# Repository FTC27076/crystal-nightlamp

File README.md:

Hi! 
this is my week 2 project in half-life and this week I'm designing a night light in the shape of a crystal!
Here's how it works:
a 4XAA battery holder with a switch carries the power to a 220 ohm resistor, which then goes to a 5V green LED strip
## Onshape Link:
https://cad.onshape.com/documents/a97c7134ccd0741b3f998674/w/13b3333805ea5d17c64ad727/e/1efaff581b8b39a1d64b4fe4

## BOM:

| Item | Qty | Supplier | Cost/item | Total Cost | link |
| :--- | :--- | :--- | :--- | :--- | :--- |
| resistor pack | 1 | E projects, LLC | $6.42 | $6.42 | https://www.amazon.ca/Projects-10EP514220R-220-Resistors-Pack/dp/B00CVZ3YOQ?source=ps-sl-shoppingads-lpcontext&ref_=fplfs&psc=1&smid=AODFMOUHD0RRM |
| LED strip lights | 1 | clearhill | $10.53 | $10.53 | https://www.amazon.ca/Clearhill-Dimmable-320LEDs-Waterproof-Decoration/dp/B0CZ6RRBV5?source=ps-sl-shoppingads-lpcontext&ref_=fplfs&th=1 |
| DAIERTEK 4 AA Battery Holder with Switch 6V Battery Case Holder with Cover 4 Slots 1.5V AA Battery Storage Box with Wire | 1 | DAIERTEK | $7.00 | $7.00 | https://www.amazon.ca/DaierTek-Battery-Holder-Storage-Connector/dp/B09N1GDWQ9?source=ps-sl-shoppingads-lpcontext&ref_=fplfs&smid=AVZNWT0O79W01&th=1 |
| 3d print/model | 1 | Snapmaker | $0.01 | $0.01 | https://cad.onshape.com/documents/a97c7134ccd0741b3f998674/w/13b3333805ea5d17c64ad727/e/1efaff581b8b39a1d64b4fe4 |
| PCB | 1 | JLC | $13.89 | $13.89 | https://trade.jlcpcb.com/checkout/payMethod?systemType=order_pcb&calType=PAY&batchNum=W2026112710500528&preOfferRate=0&spm=Jlcpcb.Confirmorder.1001 |
| Estimated total shipping | 1 | | | $7.03 | |

Images of the design ig:

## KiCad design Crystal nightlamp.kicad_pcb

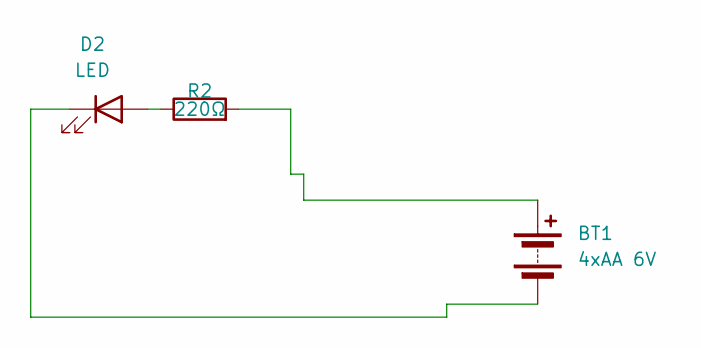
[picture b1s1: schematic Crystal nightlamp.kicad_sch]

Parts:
BT1: 4xAA 6V; SolderWire-0.5sqmm_1x02_P4.8mm_D0.9mm_OD2.3mm
D2: LED; LED_D3.0mm
R2: 220Ω; R_Axial_DIN0204_L3.6mm_D1.6mm_P5.08mm_Horizontal

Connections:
unnamed: BT1.1 (+), R2.2
unnamed: BT1.2 (-), D2.1 (K)
unnamed: D2.2 (A), R2.1

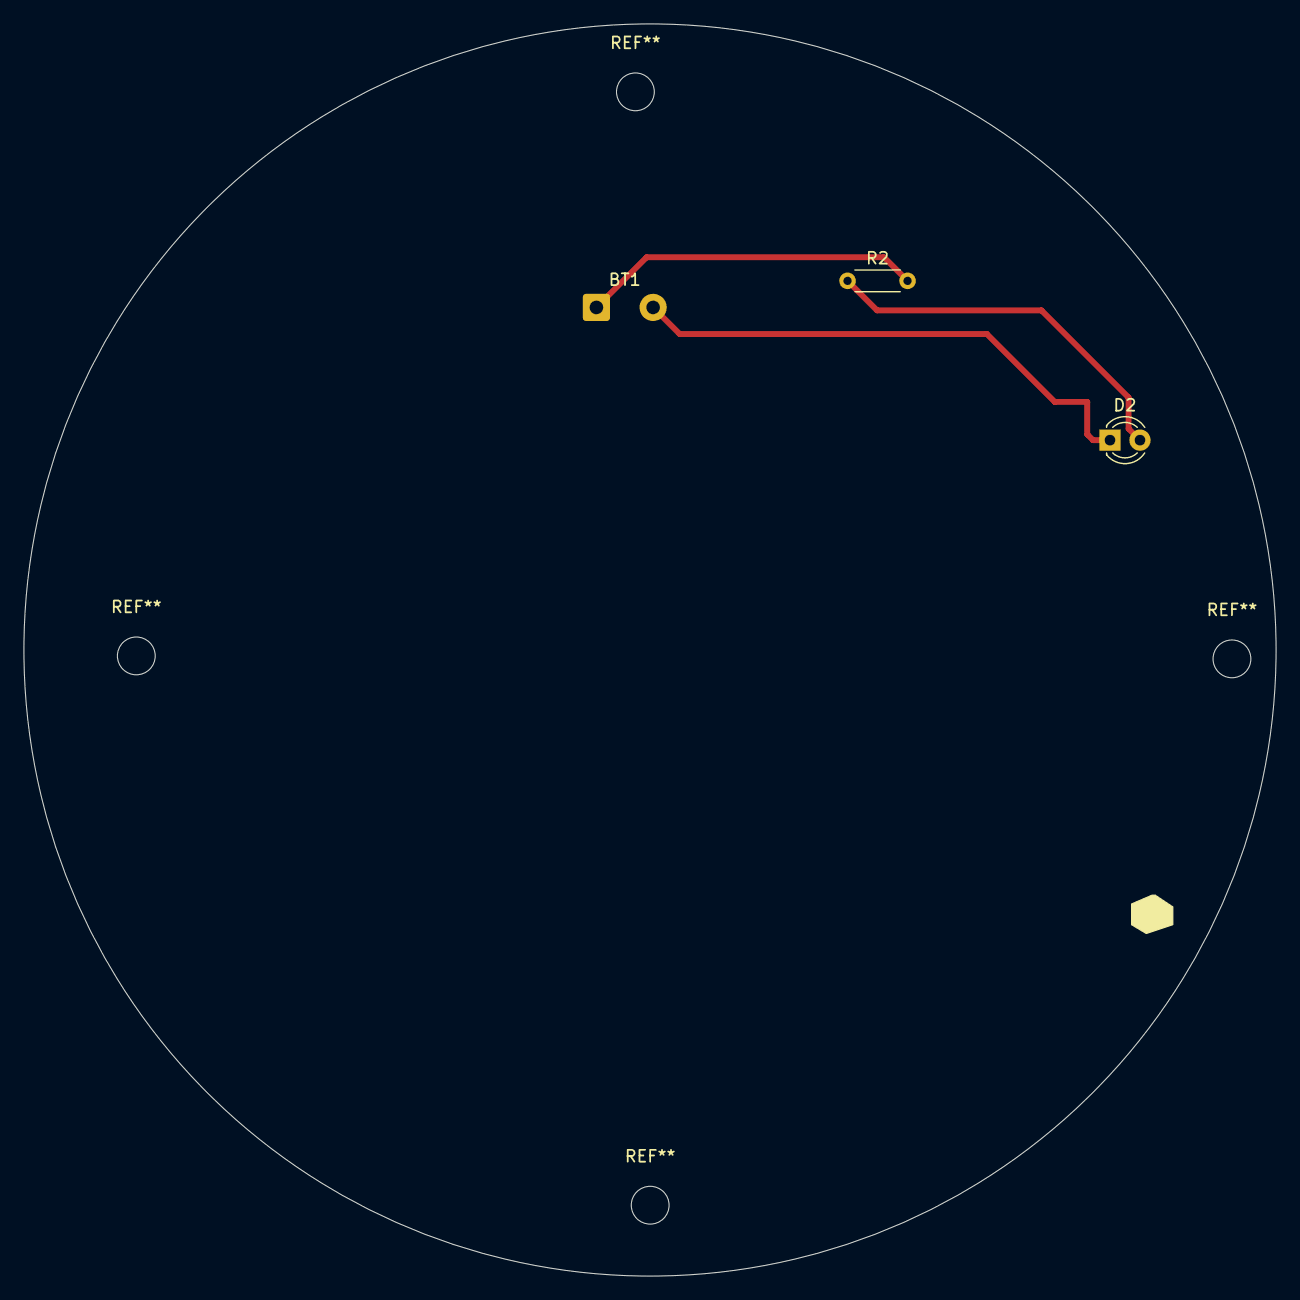
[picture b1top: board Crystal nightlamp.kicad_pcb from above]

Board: 2 copper layers, 106.0 x 106.0 mm, 3 parts (0 on the bottom side), 3 nets.
